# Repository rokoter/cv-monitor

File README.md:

# CV-monitor

Herbruikbaar ESP32-S3-sensorbord voor Home Assistant (ESPHome). Twee algemene temperatuurpoorten (TEMP 1/2,
DS18B20); eerste toepassing: aanvoer- en retourtemperatuur van de CV-installatie. Voeding via USB-C met een 18650 als
UPS-backup. Uitbreidbaar via Qwiic (I²C), een uitbreidingsheader en aansluitingen voor OLED en e-ink.

Leertraject: Koen stuurt en controleert, Claude voert uit.

## Status
| Stap | Status |
|------|--------|
| 1. Schema (KiCad) | rev 0.8 akkoord – nieuw: Resol VBus-ingang (opto-geïsoleerd) en 2 relaiskanalen, Finder 34.51 op het bord en/of extern (`docs/schema_blok10_11_vbus_relais.png`) |
| 2. PCB-layout | rev 0.3 (100 × 100 mm, VBus + relais): plaatsing in review – `docs/pcb_plaatsing_rev0.3.png`, `docs/pcb_preview_*_rev0.3.png`, 3D: `docs/pcb_3d_*_rev0.3.png`; routing volgt na akkoord. rev 0.2 (gerouteerd, DRC 0/0) is niet besteld en vervalt |
| 3. JLCPCB productie (Gerber, BOM, CPL) | rev 0.2 klaar voor offerte: Economic PCBA, ESP + through-hole zelf – `hardware/cv_monitor/production/README.md`, kosten: `docs/KOSTEN.md` |
| 4. Firmware (ESPHome) | – |
| 5. Behuizing (FreeCAD) | – |

## Mappen
| Map | Inhoud |
|-----|--------|
| `hardware/cv_monitor/` | KiCad-project (open `cv_monitor.kicad_pro`); details in de README daar |
| `generator/` | Scripts die schema en bibliotheek opbouwen en controleren (`design.py` = het ontwerp in tekst) |
| `docs/` | Schema-PDF en uitleg (draw.io) |
| `firmware/` | ESPHome-configuratie (volgt) |
| `enclosure/` | FreeCAD-behuizing (volgt) |

## PCB opnieuw genereren: plaatsing + routing
```bash
P=hardware/cv_monitor/cv_monitor
kicad-cli sch export netlist -o /tmp/cv_monitor.net $P.kicad_sch
/usr/bin/python3 generator/make_pcb.py /tmp/cv_monitor.net $P.kicad_pcb      # plaatsing + silkscreen
/usr/bin/python3 generator/route.py prep $P.kicad_pcb $P.dsn                 # vlakken, keepouts, fanout, DSN
xvfb-run -a java -jar freerouting.jar -de $P.dsn -dr generator/freerouting.rules -do $P.ses -mp 80 -mt 1
/usr/bin/python3 generator/route.py import $P.kicad_pcb $P.ses               # sporen + GND-vulling
/usr/bin/python3 generator/drc.py $P.kicad_pcb                               # moet 0 / 0 geven
/usr/bin/python3 generator/route_report.py $P.kicad_pcb                      # lengtes, breedtes, controles
```
- Plaatsing: `generator/placement.py`; ontwerpregels en netklassen: `generator/rules.py`.
- Lagen: F.Cu signaal + GND-vulling | In1 GND-vlak | In2 3V3-vlak | B.Cu signaal + GND-vulling.
- Netklassen: standaard 0,2 mm (0,15 mm vrij), 5V/VSYS/accu 0,8 mm, USB-ingang 0,5 mm, B− 0,4 mm,
  GND/3V3 0,4 mm, USB D+/D− als differentieel paar 0,25/0,15 mm (~90 Ω, schatting); via's 0,6/0,3 mm
  (vermogen 0,8/0,4 mm).
- USB: vast voorgerouteerd (`fanout.usb_preroute`): USB-C → ESD-chip U1 (180° gedraaid, zodat D−/D+
  zonder kruising doorlopen) → paar over de onderkant → ESP-pin 13/14; ~79 mm, lengteverschil < 0,5 mm.
- `route.py prep` geeft elke SMD-pad op GND/3V3 een eigen via naar het vlak (`generator/fanout.py`),
  legt de dubbele USB-C-datapinnen vast en houdt de antennezone (alle lagen) en de bovenlaag onder
  de ESP-module vrij van sporen. Freerouting (v1.9.0, open source) routeert de rest.
- Koperlagen als plaatje: `generator/render_layers.sh $P.kicad_pcb docs rev0.3`.

3D: alle footprints staan in de projectbibliotheek `cv_monitor.pretty` en de 3D-modellen (STEP) in
`hardware/cv_monitor/3dmodels` (zie de README daar). In KiCad: **Beeld → 3D-viewer** (Alt+3).
Bord met onderdelen (rev 0.3): 100 × 100 × 35,8 mm (19,1 mm onder het bord door accuhouder + cel, 15,1 mm
erboven door de relais). Snelle preview zonder KiCad: `kicad-cli pcb export step` en `generator/render_3d.py` →
`docs/pcb_3d_boven_rev0.3.png` en `docs/pcb_3d_onder_rev0.3.png`.

Plaatsingsafspraken (worden door `drc.py` mee gecontroleerd):
- alle R's, C's, diodes en LED's horizontaal (0° of 180°), kleine onderdelen in nette rijen/kolommen;
- alle silkscreentekst horizontaal, leesbaar vanuit één kant (boven: van voren, onder: met het bord omgedraaid);
- referentie bij voorkeur recht boven/onder/links/rechts van het eigen onderdeel, binnen de bordrand;
- pinnamen van headers en klemmen op de bovenkant (waar je aansluit), één naam per regel links van de pin;
- polariteit (+) bij de accu en bij de accu-omgekeerd-LED, op boven- en onderkant;
- achterkant: blokschema van de werking (`generator/back_diagram.py`), titel bovenaan tussen de montagegaten;
- geen THT-pin door een onderdeel aan de andere kant (accuhouder);
- 230 V (relaiscontacten NO/COM/NC + klemmen J12/J13): gestippeld kader op boven- en onderkant met
  '230V~ 5A', en al het koper van andere netten (alle lagen, ook gaten) minstens 8 mm van het 230 V-koper
  (`pcb_checks.mains_clearance`; krapste plek nu 8,3 mm: spoelpad K1.A2 ↔ NO-pad K2).

## Productiebestanden (JLCPCB)
```bash
P=hardware/cv_monitor/cv_monitor
/usr/bin/python3 generator/sync_attrs.py $P.kicad_pcb            # LCSC/DNP uit design.py, routing blijft
/usr/bin/python3 generator/make_production.py $P.kicad_pcb rev0.2  # Gerber-zip, BOM, CPL
```
Uitvoer en bestelchecklist: `hardware/cv_monitor/production/`. JLCPCB-draaiingscorrecties staan in
`make_production.py` (`ROT_FIX`); gepolariseerde onderdelen altijd in de JLCPCB-preview controleren.

## Opnieuw bouwen en controleren
```bash
./generator/build.sh
```
Genereert het schema uit `generator/design.py`, laat KiCad de netlist exporteren en vergelijkt die
pin voor pin met de bedoeling (kortsluitingen, losse pinnen, voeding). Daarnaast: ERC in KiCad zelf.

## KiCad-versie
De bestanden worden gemaakt met **KiCad 7.0** (het formaat dat de generator schrijft). Openen, bekijken
en ERC draaien kan prima in KiCad 8, 9 of 10. **Sla ze in een nieuwere versie niet op over de repo-bestanden**:
KiCad zet ze dan om naar het nieuwe formaat, dat KiCad 7 niet meer kan lezen. Wil je iets aanpassen,
geef het door (of sla op als kopie); de wijziging komt dan via `design.py` in het ontwerp.

## Werkwijze
- Elke ontwerpwijziging is een eigen commit; goedgekeurde stappen krijgen een tag (bijv. `schema-v1.0`).
- Wijzig het schema bij voorkeur via `design.py` + `build.sh`, zodat de controle blijft kloppen.
  Handmatige aanpassingen in KiCad kunnen ook, maar worden bij een volgende generatie overschreven.

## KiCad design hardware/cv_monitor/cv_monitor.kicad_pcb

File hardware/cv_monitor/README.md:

# CV temperatuurmonitor – stap 1: schema (rev 0.8)

Herbruikbaar ESP32-S3-sensorbord: meet 2 temperaturen met DS18B20's (bijv. CV-aanvoer en -retour),
heeft een 18650 als UPS-backup, laadt/werkt via USB-C en heeft aansluitingen voor Qwiic-modules,
een OLED (I²C) en een e-ink-display (SPI). Sinds rev 0.8 ook een Resol VBus-ingang (zonne-/boilerregelaar)
en 2 relaisuitgangen (relais op het bord en/of extern).

## Openen
Pak de map uit en open `cv_monitor.kicad_pro` in KiCad (7, 8 of 9). De projectbibliotheken
(`cv_monitor.kicad_sym`, `cv_monitor.pretty`) worden via `sym-lib-table`/`fp-lib-table` automatisch geladen.
Gemaakt in KiCad 7-formaat; KiCad 8/9 vraagt bij opslaan om te converteren – dat is prima.

## Blokken
| # | Blok | Kern |
|---|------|------|
| 1 | USB-C | 1,1 A PTC-zekering, 5,1k CC-weerstanden, USBLC6 ESD op D+/D- (native USB) |
| 2 | Lader | TP4056, 600 mA (R3 = 2k), rode/groene LED, optionele NTC op J9 (JP1 doorsnijden) |
| 3 | Power-path | SS34 + AO3401A: USB voedt systeem, accu neemt naadloos over; AP2112K-3.3 LDO |
| 4 | Accu | 18650 + ompoolbeveiliging (Q3) + fout-LED D5 + DW01A + AO8810 (8205A-type dubbele MOSFET; onder-/overspanning, overstroom) |
| 5 | ESP32-S3-WROOM-1-N8 | 8 MB flash, alle GPIO's op het symbool |
| 6 | Metingen | VBAT, USB aanwezig, 2 sensorpoorten (4,7k pull-up, 100R serie) |
| 7 | Bediening | RESET, BOOT, STATUS-knop, status-LED, uitbreidingsheader J4 (DNP) |
| 8 | Qwiic | 2× JST-SH, I²C met 4,7k pull-ups |
| 9 | Displays | J8 e-ink (SPI, Waveshare-volgorde), J7 OLED (I²C) – beide DNP |
| 10 | Resol VBus | J10, opto-coupler U6 (LTV-817S): alleen lezen, Resol-massa gescheiden van GND, RX = GPIO38 |
| 11 | Relais | 2× AO3400A (GPIO35/36) + vrijloop + status-LED; per kanaal Finder 34.51 (5 V) op het bord (J12/J13, 230 V~ max 5 A) en/of extern relais op J11 (V+/REL1/REL2/GND) |
| – | Testpunten | TP1–TP5: VBUS, VSYS, BAT+, 3V3, GND (alleen koperpads) |

## GPIO-overzicht (ESP32-S3)
| GPIO | Functie | GPIO | Functie |
|------|---------|------|---------|
| 0 | BOOT-knop | 13 | e-ink DC |
| 1 | VBAT meting (ADC1) | 14 | e-ink RST |
| 2 | USB aanwezig (ADC1) | 15 | STATUS-knop |
| 3 | vrij (strapping) | 16 | status-LED |
| 35/36 | relais 1/2 | 38 | Resol VBus RX |
| 4 | TEMP 1 (1-Wire) | 17/18 | uitbreiding J4 |
| 5 | TEMP 2 (1-Wire) | 19/20 | USB D-/D+ |
| 6/7 | uitbreiding J4 (ADC1) | 21 | e-ink BUSY |
| 8 | I²C SDA (Qwiic + OLED) | 43/44 | UART TX/RX (J4) |
| 9 | I²C SCL (Qwiic + OLED) | 45/46 | vrij (strapping) |
| 10 | e-ink CS | overige | vrij (X op schema) |
| 11 | e-ink DIN (MOSI) | | |
| 12 | e-ink CLK | | |

## Controle door jou
1. Open het schema en draai **Inspect → Electrical Rules Checker**. Verwacht: 0 fouten.
2. Loop elk blok na met de notities op het blad.
3. LCSC-nummers staan als veld `LCSC` per onderdeel; die worden in de BOM-stap opnieuw gecontroleerd.

## Gebruik / aandachtspunten
- Voeding via een USB-lader van minimaal 1 A (laden 0,6 A + systeem); een pc-poort levert te weinig.
- Na het plaatsen van de accu één keer USB aansluiten: dan activeert de DW01A de accu-uitgang.
- Accuhouder: MPD BK-18650-PC2 (de footprint past alleen op deze houder).
- Accu-NTC (optioneel): stekker in J9 aan de bovenkant, de draad door de sleuf (4 × 7 mm) eronder naar
  de onderkant en de NTC met kaptontape midden op de cel. Bij gebruik van een NTC: JP1 doorsnijden.
  De sleuf is groot genoeg om ook een JST-PH-stekkertje in de lengte door te steken.

## Productie
Gerber, BOM, CPL en de bestelchecklist voor JLCPCB: `production/README.md`.
Gekozen: accuhouder MPD BK-18650-PC2, schroefklemmen 3,5 mm; J7/J8 volgen de pinvolgorde van een
0,96" SSD1306-OLED (GND-VCC-SCL-SDA) en een Waveshare 2,9" e-Paper V2 (8-pins).

## Documentatie
- `../../docs/accubeveiliging_DW01A_FS8205A.drawio`: uitleg hoe de accubeveiliging werkt (openen op app.diagrams.net).

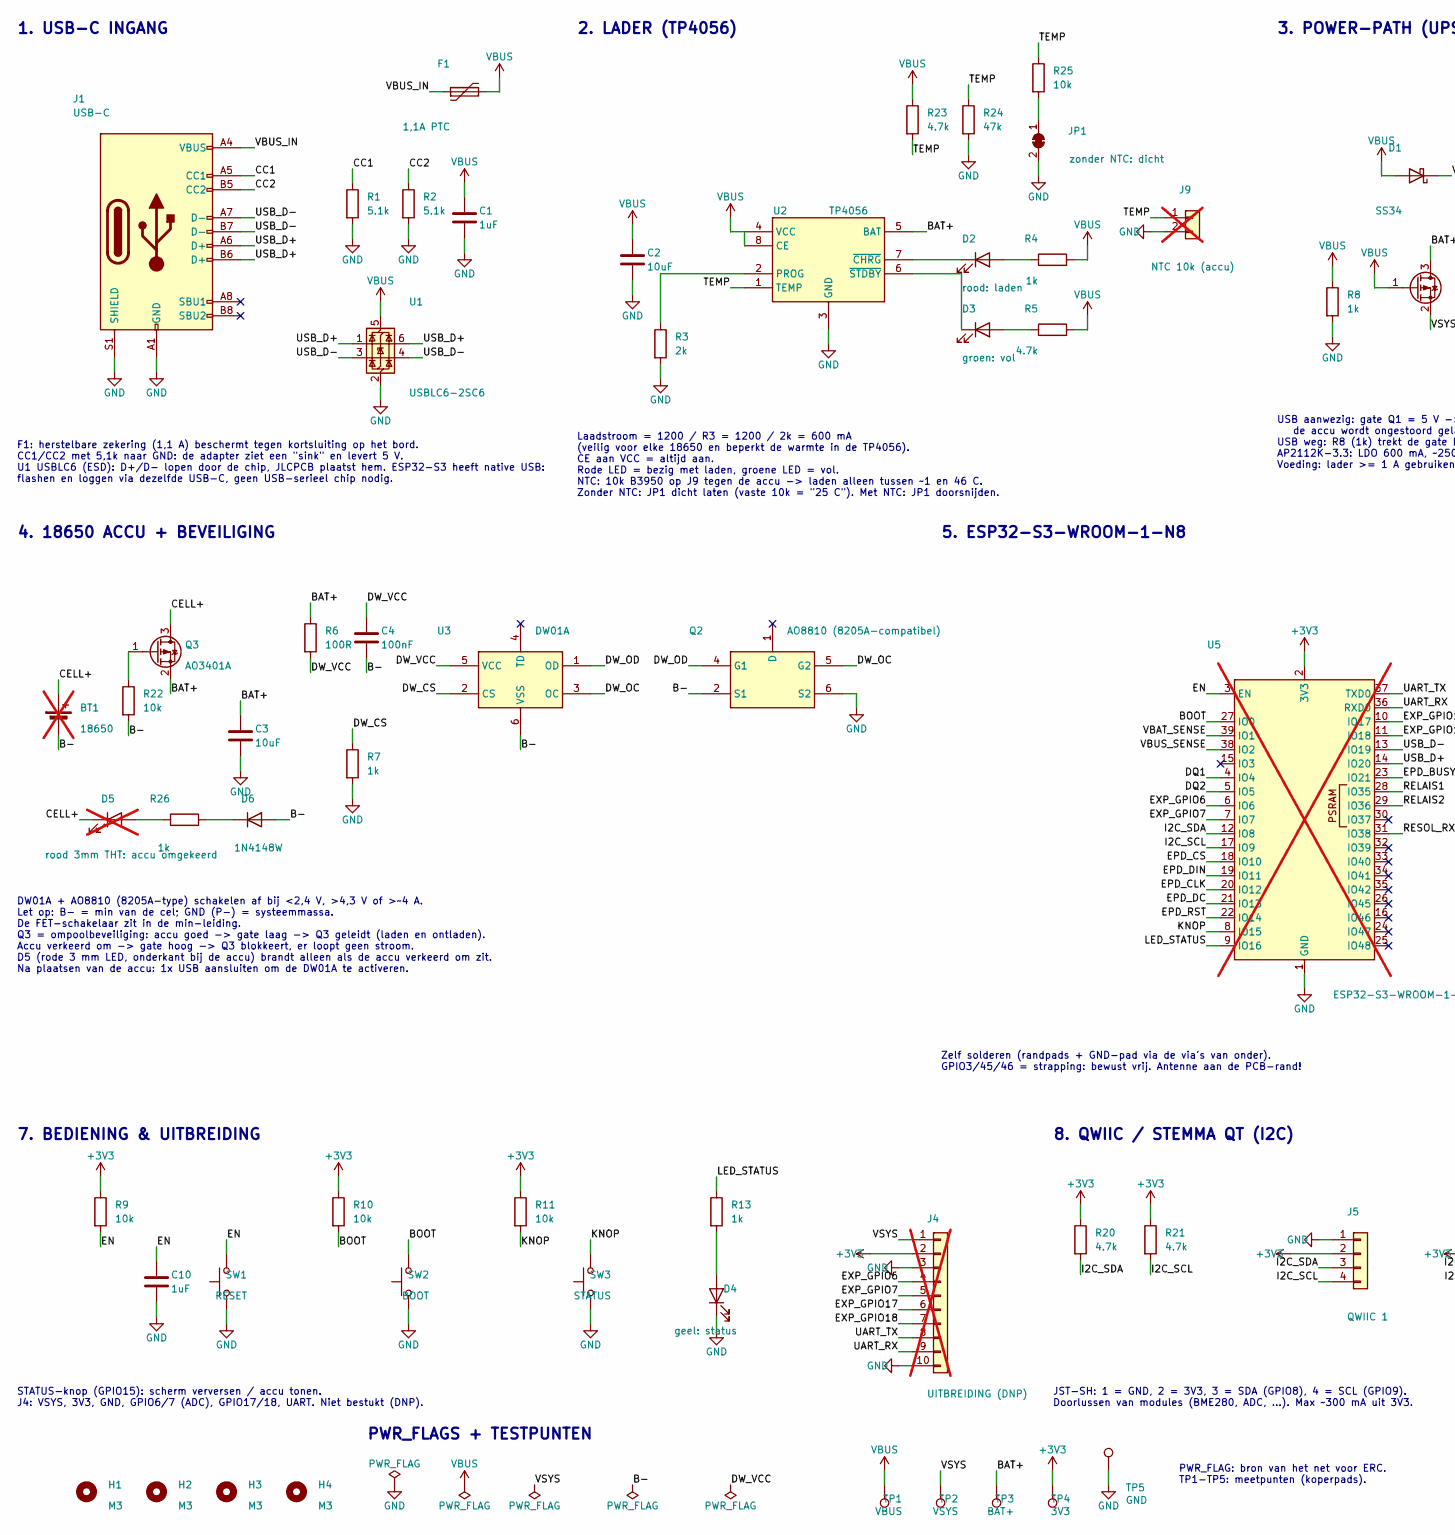
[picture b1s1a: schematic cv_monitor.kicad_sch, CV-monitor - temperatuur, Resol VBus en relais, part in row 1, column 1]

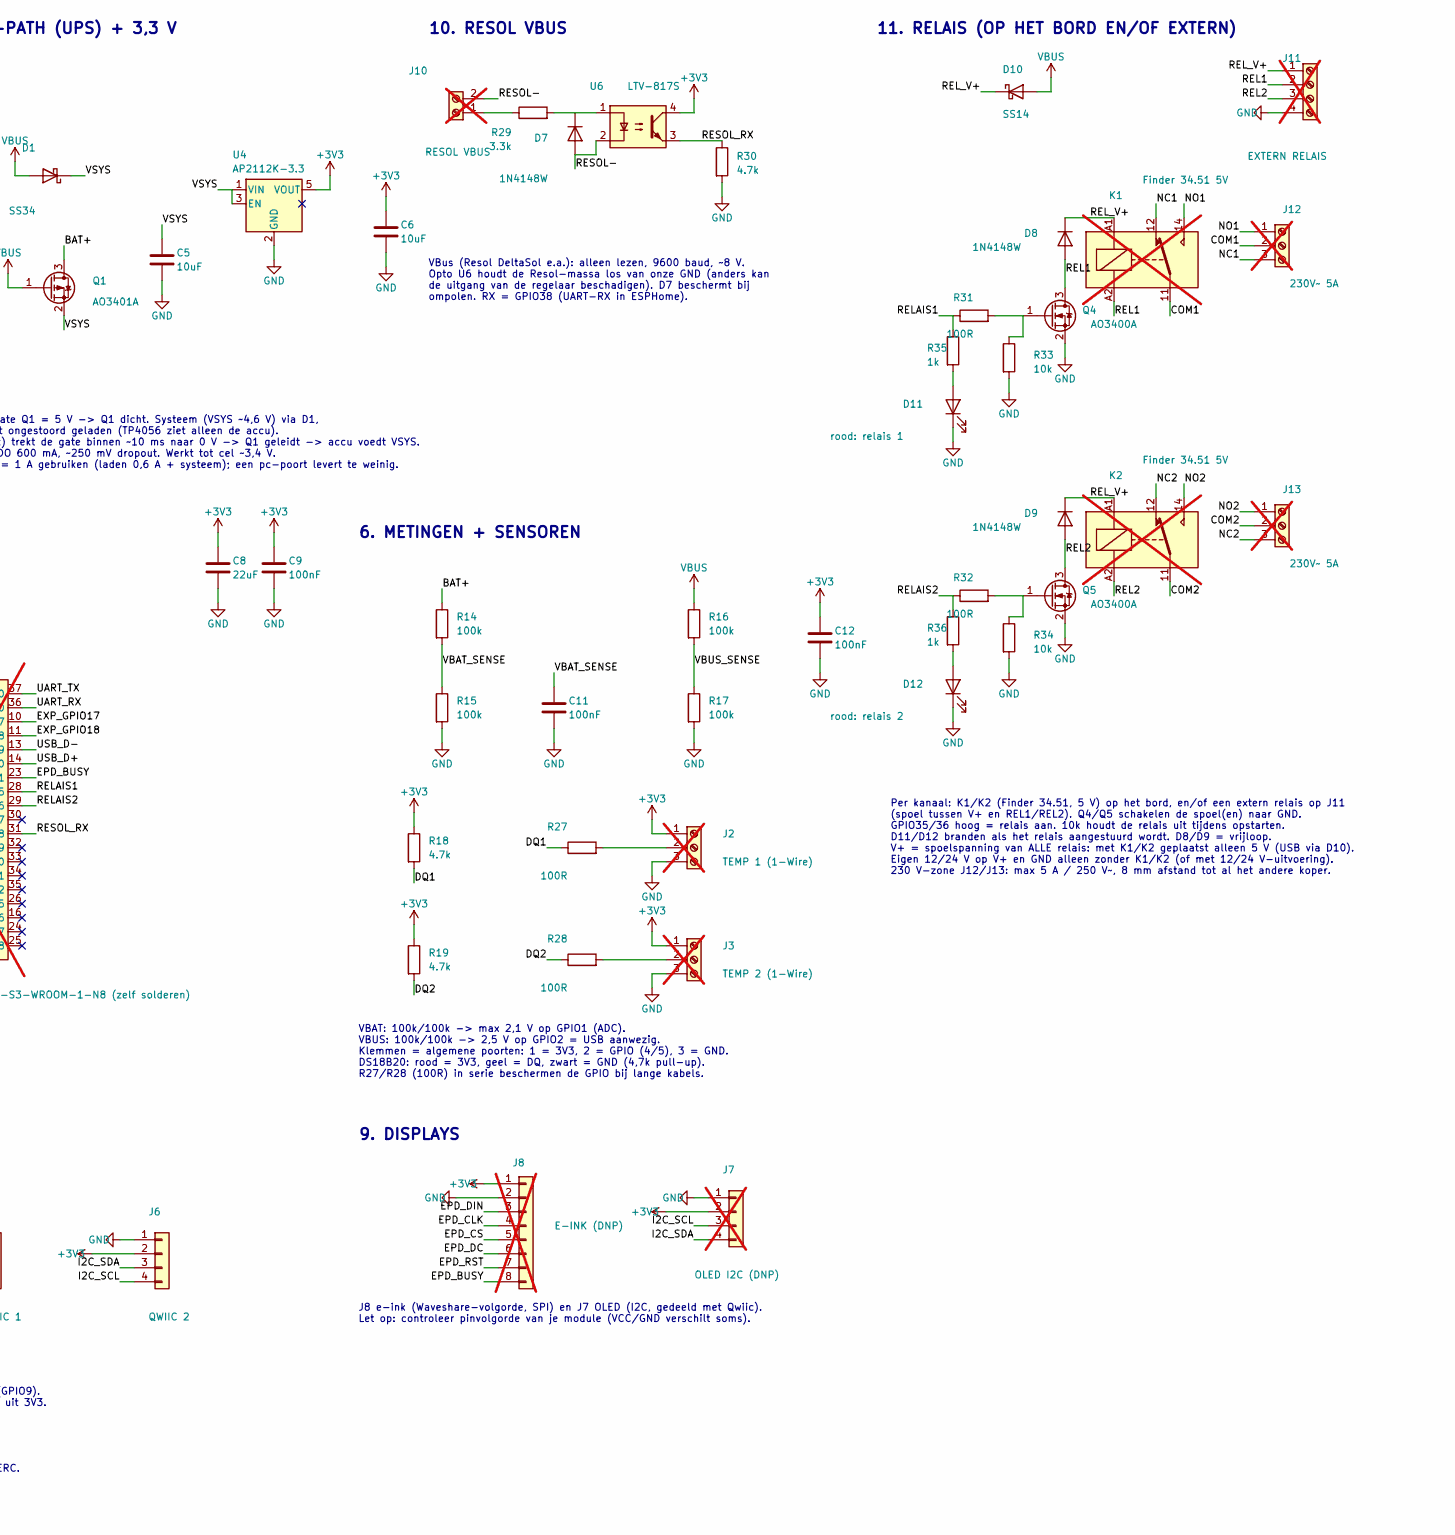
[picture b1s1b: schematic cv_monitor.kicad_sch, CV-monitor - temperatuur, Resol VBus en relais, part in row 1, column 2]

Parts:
BT1: 18650; BatteryHolder_MPD_BH-18650-PC2; MPN houder MPD BK-18650-PC2; not fitted
C1, C10: 1uF; C_0603_1608Metric; LCSC C15849
C2, C3, C5, C6: 10uF; C_0805_2012Metric; LCSC C15850
C4, C9, C11, C12: 100nF; C_0603_1608Metric; LCSC C14663
C8: 22uF; C_0805_2012Metric; LCSC C45783
D1: SS34; D_SMA; LCSC C8678
D2: rood: laden; LED_0603_1608Metric; LCSC C2286
D3: groen: vol; LED_0603_1608Metric; LCSC C12624
D4: geel: status; LED_0603_1608Metric; LCSC C89811
D5: rood 3mm THT: accu omgekeerd; LED_D3.0mm; not fitted
D6, D7, D8, D9: 1N4148W; D_SOD-123; LCSC C81598
D10: SS14; D_SMA; LCSC C2480
D11: rood: relais 1; LED_0603_1608Metric; LCSC C2286
D12: rood: relais 2; LED_0603_1608Metric; LCSC C2286
F1: 1,1A PTC; Fuse_1206_3216Metric; LCSC C269119
H1, H2, H3, H4: M3; MountingHole_3.2mm_M3
J1: USB-C; USB_C_Receptacle_HRO_TYPE-C-31-M-12; LCSC C165948
J2: TEMP 1 (1-Wire); TerminalBlock_Phoenix_PT-1,5-3-3.5-H_1x03_P3.50mm_Horizontal; not fitted
J3: TEMP 2 (1-Wire); TerminalBlock_Phoenix_PT-1,5-3-3.5-H_1x03_P3.50mm_Horizontal; not fitted
J4: UITBREIDING (DNP); PinHeader_1x10_P2.54mm_Vertical; not fitted
J5: QWIIC 1; JST_SH_SM04B-SRSS-TB_1x04-1MP_P1.00mm_Horizontal; LCSC C160404
J6: QWIIC 2; JST_SH_SM04B-SRSS-TB_1x04-1MP_P1.00mm_Horizontal; LCSC C160404
J7: OLED I2C (DNP); PinHeader_1x04_P2.54mm_Vertical; not fitted
J8: E-INK (DNP); PinHeader_1x08_P2.54mm_Vertical; not fitted
J9: NTC 10k (accu); JST_PH_B2B-PH-K_1x02_P2.00mm_Vertical; not fitted
J10: RESOL VBUS; TerminalBlock_Phoenix_PT-1,5-2-3.5-H_1x02_P3.50mm_Horizontal; not fitted
J11: EXTERN RELAIS; TerminalBlock_Phoenix_PT-1,5-4-3.5-H_1x04_P3.50mm_Horizontal; not fitted
J12, J13: 230V~ 5A; TerminalBlock_Phoenix_MKDS-1,5-3-5.08_1x03_P5.08mm_Horizont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; MPN Phoenix MKDS 1,5/3-5,08; not fitted
JP1: zonder NTC: dicht; SolderJumper-2_P1.3mm_Bridged_RoundedPad1.0x1.5mm
K1, K2: Finder 34.51 5V; Relay_SPDT_Finder_34.51_Vertical; MPN Finder 34.51.7.005.0010; not fitted
Q1, Q3: AO3401A; SOT-23; LCSC C15127
Q2: AO8810 (8205A-compatibel); TSSOP-8_4.4x3mm_P0.65mm; LCSC C21426
Q4, Q5: AO3400A; SOT-23; LCSC C20917
R1, R2: 5.1k; R_0603_1608Metric; LCSC C23186
R3: 2k; R_0603_1608Metric; LCSC C22975
R4, R7, R8, R13, R26, R35, R36: 1k; R_0603_1608Metric; LCSC C21190
R5, R18, R19, R20, R21, R23, R30: 4.7k; R_0603_1608Metric; LCSC C23162
R6, R27, R28, R31, R32: 100R; R_0603_1608Metric; LCSC C22775
R9, R10, R11, R22, R25, R33, R34: 10k; R_0603_1608Metric; LCSC C25804
R14, R15, R16, R17: 100k; R_0603_1608Metric; LCSC C25803
R24: 47k; R_0603_1608Metric; LCSC C25819
R29: 3.3k; R_0603_1608Metric; LCSC C22978
SW1: RESET; SW_Push_1P1T_XKB_TS-1187A; LCSC C318884
SW2: BOOT; SW_Push_1P1T_XKB_TS-1187A; LCSC C318884
SW3: STATUS; SW_Push_1P1T_XKB_TS-1187A; LCSC C318884
TP1: VBUS; TestPoint_Pad_D1.5mm
TP2: VSYS; TestPoint_Pad_D1.5mm
TP3: BAT+; TestPoint_Pad_D1.5mm
TP4: 3V3; TestPoint_Pad_D1.5mm
TP5: GND; TestPoint_Pad_D1.5mm
U1: USBLC6-2SC6; SOT-23-6; LCSC C7519
U2: TP4056; SOIC-8-1EP_3.9x4.9mm_P1.27mm_EP2.41x3.3mm_ThermalVias_0.3mm; LCSC C16581
U3: DW01A; SOT-23-6; LCSC C351410
U4: AP2112K-3.3; SOT-23-5; LCSC C51118
U5: ESP32-S3-WROOM-1-N8 (zelf solderen); ESP32-S3-WROOM-1_HandSolder; LCSC C2913198; not fitted
U6: LTV-817S; SMDIP-4_W9.53mm; LCSC C109227

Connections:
+3V3: C6.1, C8.1, C9.1, C12.1, J2.1, J3.1, J4.2, J5.2, J6.2, J7.2, J8.1, R9.1, R10.1, R11.1, R18.1, R19.1, R20.1, R21.1, TP4.1, U4.5 (VOUT), U5.2 (3V3), U6.4
B-: BT1.2 (-), C4.2, D6.2 (A), Q2.2 (S1), Q2.3 (S1), R22.2, U3.6 (VSS)
BAT+: C3.1, Q1.3 (D), Q3.2 (S), R6.1, R14.1, TP3.1, U2.5 (BAT)
BOOT: R10.2, SW2.2, U5.27 (IO0)
CC1: J1.A5 (CC1), R1.1
CC2: J1.B5 (CC2), R2.1
CELL+: BT1.1 (+), D5.1 (K), Q3.3 (D)
COM1: J12.2, K1.11
COM2: J13.2, K2.11
DQ1: R18.2, R27.1, U5.4 (IO4)
DQ2: R19.2, R28.1, U5.5 (IO5)
DW_CS: R7.1, U3.2 (CS)
DW_OC: Q2.5 (G2), U3.3 (OC)
DW_OD: Q2.4 (G1), U3.1 (OD)
DW_VCC: C4.1, R6.2, U3.5 (VCC)
EN: C10.1, R9.2, SW1.2, U5.3 (EN)
EPD_BUSY: J8.8, U5.23 (IO21)
EPD_CLK: J8.4, U5.20 (IO12)
EPD_CS: J8.5, U5.18 (IO10)
EPD_DC: J8.6, U5.21 (IO13)
EPD_DIN: J8.3, U5.19 (IO11)
EPD_RST: J8.7, U5.22 (IO14)
EXP_GPIO6: J4.4, U5.6 (IO6)
EXP_GPIO7: J4.5, U5.7 (IO7)
EXP_GPIO17: J4.6, U5.10 (IO17)
EXP_GPIO18: J4.7, U5.11 (IO18)
GND: C1.2, C2.2, C3.2, C5.2, C6.2, C8.2, C9.2, C10.2, C11.2, C12.2, D4.1 (K), D11.1 (K), D12.1 (K), J1.A1 (GND), J1.A12 (GND), J1.B1 (GND), J1.B12 (GND), J1.S1 (SHIELD), J2.3, J3.3, J4.3, J4.10, J5.1, J6.1, J7.1, J8.2, J9.2, J11.4, JP1.2 (B), Q2.6 (S2), Q2.7 (S2), Q4.2 (S), Q5.2 (S), R1.2, R2.2, R3.2, R7.2, R8.2, R15.2, R17.2, R24.2, R30.2, R33.2, R34.2, SW1.1, SW2.1, SW3.1, TP5.1, U1.2 (GND), U2.3 (GND), U2.9 (EP), U4.2 (GND), U5.1 (GND), U5.40 (GND), U5.41 (GND)
I2C_SCL: J5.4, J6.4, J7.3, R21.2, U5.17 (IO9)
I2C_SDA: J5.3, J6.3, J7.4, R20.2, U5.12 (IO8)
KNOP: R11.2, SW3.2, U5.8 (IO15)
LED_STATUS: R13.1, U5.9 (IO16)
NC1: J12.3, K1.12
NC2: J13.3, K2.12
NO1: J12.1, K1.14
NO2: J13.1, K2.14
unnamed: D2.2 (A), R4.1
unnamed: D2.1 (K), U2.7 (~CHRG)
unnamed: D3.2 (A), R5.1
unnamed: D3.1 (K), U2.6 (~STDBY)
unnamed: D4.2 (A), R13.2
unnamed: D5.2 (A), R26.1
unnamed: D6.1 (K), R26.2
unnamed: D7.1 (K), R29.2, U6.1
unnamed: D11.2 (A), R35.2
unnamed: D12.2 (A), R36.2
unnamed: J2.2, R27.2
unnamed: J3.2, R28.2
unnamed: J10.1, R29.1
unnamed: JP1.1 (A), R25.2
unnamed: Q3.1 (G), R22.1
unnamed: Q4.1 (G), R31.2, R33.1
unnamed: Q5.1 (G), R32.2, R34.1
unnamed: R3.1, U2.2 (PROG)
REL1: D8.2 (A), J11.2, K1.A2, Q4.3 (D)
REL2: D9.2 (A), J11.3, K2.A2, Q5.3 (D)
RELAIS1: R31.1, R35.1, U5.28 (IO35)
RELAIS2: R32.1, R36.1, U5.29 (IO36)
REL_V+: D8.1 (K), D9.1 (K), D10.1 (K), J11.1, K1.A1, K2.A1
RESOL-: D7.2 (A), J10.2, U6.2
RESOL_RX: R30.1, U5.31 (IO38), U6.3
TEMP: J9.1, R23.2, R24.1, R25.1, U2.1 (TEMP)
UART_RX: J4.9, U5.36 (RXD0)
UART_TX: J4.8, U5.37 (TXD0)
USB_D+: J1.A6 (D+), J1.B6 (D+), U1.1 (I/O1), U1.6 (I/O1), U5.14 (IO20)
USB_D-: J1.A7 (D-), J1.B7 (D-), U1.3 (I/O2), U1.4 (I/O2), U5.13 (IO19)
VBAT_SENSE: C11.1, R14.2, R15.1, U5.39 (IO1)
VBUS: C1.1, C2.1, D1.2 (A), D10.2 (A), F1.2, Q1.1 (G), R4.2, R5.2, R8.1, R16.1, R23.1, TP1.1, U1.5 (VBUS), U2.4 (VCC), U2.8 (CE)
VBUS_IN: F1.1, J1.A4 (VBUS), J1.A9 (VBUS), J1.B4 (VBUS), J1.B9 (VBUS)
VBUS_SENSE: R16.2, R17.1, U5.38 (IO2)
VSYS: C5.1, D1.1 (K), J4.1, Q1.2 (S), TP2.1, U4.1 (VIN), U4.3 (EN)

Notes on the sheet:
1. USB-C INGANG
F1: herstelbare zekering (1,1 A) beschermt tegen kortsluiting op het bord. CC1/CC2 met 5,1k naar GND: de adapter ziet een "sink" en levert 5 V. U1 USBLC6 (ESD): D+/D- lopen door de chip, JLCPCB plaatst hem. ESP32-S3 heeft native USB: flashen en loggen via dezelfde USB-C, geen USB-serieel chip nodig.
2. LADER (TP4056)
Laadstroom = 1200 / R3 = 1200 / 2k = 600 mA (veilig voor elke 18650 en beperkt de warmte in de TP4056). CE aan VCC = altijd aan. Rode LED = bezig met laden, groene LED = vol. NTC: 10k B3950 op J9 tegen de accu -> laden alleen tussen ~1 en 46 C. Zonder NTC: JP1 dicht laten (vaste 10k = "25 C"). Met 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
3. POWER-PATH (UPS) + 3,3 V
USB aanwezig: gate Q1 = 5 V -> Q1 dicht. Systeem (VSYS ~4,6 V) via D1, de accu wordt ongestoord geladen (TP4056 ziet alleen de accu). USB weg: R8 (1k) trekt de gate binnen ~10 ms naar 0 V -> Q1 geleidt -> accu voedt VSYS. AP2112K-3.3: LDO 600 mA, ~250 mV dropout. Werkt tot cel ~3,4 V. Voeding: lade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
PWR_FLAGS + TESTPUNTEN
PWR_FLAG: bron van het net voor ERC. TP1-TP5: meetpunten (koperpads).
10. RESOL VBUS
VBus (Resol DeltaSol e.a.): alleen lezen, 9600 baud, ~8 V. Opto U6 houdt de Resol-massa los van onze GND (anders kan de uitgang van de regelaar beschadigen). D7 beschermt bij ompolen. RX = GPIO38 (UART-RX in ESPHome).
11. RELAIS (OP HET BORD EN/OF EXTERN)
Per kanaal: K1/K2 (Finder 34.51, 5 V) op het bord, en/of een extern relais op J11 (spoel tussen V+ en REL1/REL2). Q4/Q5 schakelen de spoel(en) naar GND. GPIO35/36 hoog = relais aan. 10k houdt de relais uit tijdens opstarten. D11/D12 branden als het relais aangestuurd wordt. D8/D9 = vrijloop. V+ = s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
4. 18650 ACCU + BEVEILIGING
DW01A + AO8810 (8205A-type) schakelen af bij <2,4 V, >4,3 V of >~4 A. Let op: B- = min van de cel; GND (P-) = systeemmassa. De FET-schakelaar zit in de min-leiding. Q3 = ompoolbeveiliging: accu goed -> gate laag -> Q3 geleidt (laden en ontladen). Accu verkeerd om -> gate hoog -> Q3 blokkeert, er lo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
5. ESP32-S3-WROOM-1-N8
Zelf solderen (randpads + GND-pad via de via's van onder). GPIO3/45/46 = strapping: bewust vrij. Antenne aan de PCB-rand!
6. METINGEN + SENSOREN
VBAT: 100k/100k -> max 2,1 V op GPIO1 (ADC). VBUS: 100k/100k -> 2,5 V op GPIO2 = USB aanwezig. Klemmen = algemene poorten: 1 = 3V3, 2 = GPIO (4/5), 3 = GND. DS18B20: rood = 3V3, geel = DQ, zwart = GND (4,7k pull-up). R27/R28 (100R) in serie beschermen de GPIO bij lange kabels.
7. BEDIENING & UITBREIDING
STATUS-knop (GPIO15): scherm verversen / accu tonen. J4: VSYS, 3V3, GND, GPIO6/7 (ADC), GPIO17/18, UART. Niet bestukt (DNP).
8. QWIIC / STEMMA QT (I2C)
JST-SH: 1 = GND, 2 = 3V3, 3 = SDA (GPIO8), 4 = SCL (GPIO9). Doorlussen van modules (BME280, ADC, ...). Max ~300 mA uit 3V3.
9. DISPLAYS
J8 e-ink (Waveshare-volgorde, SPI) en J7 OLED (I2C, gedeeld met Qwiic). Let op: controleer pinvolgorde van je module (VCC/GND verschilt soms).

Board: 4 copper layers, 99 parts (2 on the bottom side), 70 nets, no tracks yet.

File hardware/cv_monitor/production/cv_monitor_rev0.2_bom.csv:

Comment,Designator,Footprint,LCSC Part #
1uF,"C1,C10",C_0603_1608Metric,C15849
10uF,"C2,C3,C5,C6",C_0805_2012Metric,C15850
100nF,"C4,C9,C11,C12",C_0603_1608Metric,C14663
22uF,C8,C_0805_2012Metric,C45783
SS34,D1,D_SMA,C8678
rood: laden,D2,LED_0603_1608Metric,C2286
groen: vol,D3,LED_0603_1608Metric,C12624
geel: status,D4,LED_0603_1608Metric,C89811
1N4148W,D6,D_SOD-123,C81598
"1,1A PTC",F1,Fuse_1206_3216Metric,C269119
USB-C,J1,USB_C_Receptacle_HRO_TYPE-C-31-M-12,C165948
QWIIC 1 / QWIIC 2,"J5,J6",JST_SH_SM04B-SRSS-TB_1x04-1MP_P1.00mm_Horizontal,C160404
AO3401A,"Q1,Q3",SOT-23,C15127
AO8810 (8205A-compatibel),Q2,TSSOP-8_4.4x3mm_P0.65mm,C21426
5.1k,"R1,R2",R_0603_1608Metric,C23186
2k,R3,R_0603_1608Metric,C22975
1k,"R4,R7,R8,R13,R26",R_0603_1608Metric,C21190
4.7k,"R5,R18,R19,R20,R21,R23",R_0603_1608Metric,C23162
100R,"R6,R27,R28",R_0603_1608Metric,C22775
10k,"R9,R10,R11,R22,R25",R_0603_1608Metric,C25804
100k,"R14,R15,R16,R17",R_0603_1608Metric,C25803
47k,R24,R_0603_1608Metric,C25819
RESET / BOOT / STATUS,"SW1,SW2,SW3",SW_Push_1P1T_XKB_TS-1187A,C318884
USBLC6-2SC6,U1,SOT-23-6,C7519
TP4056,U2,SOIC-8-1EP_3.9x4.9mm_P1.27mm_EP2.41x3.3mm_ThermalVias_0.3mm,C16581
DW01A,U3,SOT-23-6,C351410
AP2112K-3.3,U4,SOT-23-5,C51118

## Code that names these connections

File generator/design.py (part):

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         fp='cv_monitor:ESP32-S3-WROOM-1_HandSolder', lcsc='C2913198', dnp=True, ref_at=(89, 49.5), val_at=(98, 74.5),
         nets={'2': '+3V3', '1': 'GND', '40': 'GND', '41': 'GND', '3': 'EN', '27': 'BOOT',
               '39': 'VBAT_SENSE', '38': 'VBUS_SENSE', '15': 'NC', '4': 'DQ1', '5': 'DQ2',
               '6': 'EXP_GPIO6', '7': 'EXP_GPIO7', '12': 'I2C_SDA', '17': 'I2C_SCL',
               '18': 'EPD_CS', '19': 'EPD_DIN', '20': 'EPD_CLK', '21': 'EPD_DC', '22': 'EPD_RST',
               '8': 'KNOP', '9': 'LED_STATUS', '10': 'EXP_GPIO17', '11': 'EXP_GPIO18',
               '13': 'USB_D-', '14': 'USB_D+', '23': 'EPD_BUSY', '37': 'UART_TX', '36': 'UART_RX',
               '28': 'RELAIS1', '29': 'RELAIS2', '31': 'RESOL_RX',
               **{n: 'NC' for n in ['16', '24', '25', '26', '30', '32', '33', '34', '35']}}),
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    dict(ref='J4', lib='Connector_Generic:Conn_01x10', value='UITBREIDING (DNP)', gx=70, gy=96, dnp=True,
         pwr_rotate=True, stub={'2': 7.62}, fp='Connector_PinHeader_2.54mm:PinHeader_1x10_P2.54mm_Vertical',
         ref_at=(69, 90.5), val_at=(69, 103),
         nets={'1': 'VSYS', '2': '+3V3', '3': 'GND', '4': 'EXP_GPIO6', '5': 'EXP_GPIO7', '6': 'EXP_GPIO17',
               '7': 'EXP_GPIO18', '8': 'UART_TX', '9': 'UART_RX', '10': 'GND'}),

    # ------------------------------------------------------------ 8. Qwiic / STEMMA QT (I2C)
    R('R20', '4.7k', 80, 92, '+3V3', 'I2C_SDA'),
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    dict(ref='D10', lib='Diode:SS14', value='SS14', gx=173, gy=10, fp='Diode_SMD:D_SMA', lcsc='C2480',
         ref_at=(172, 8.4), val_at=(172, 11.6), nets={'1': 'REL_V+', '2': 'VBUS'}),
    # kanaal 1: GPIO -> R31 -> Q4; K1 op het bord en/of extern relais op J11
    R('R31', '100', 170, 26, 'RELAIS1', 'REL1_G', rot=90, label_wired={'1': True},
      ref_at=(170, 24.7), val_at=(170, 27.3)),
    dict(ref='Q4', lib='Transistor_FET:AO3400A', value='AO3400A', gx=175.5, gy=26, fp='Package_TO_SOT_SMD:SOT-23',
         lcsc='C20917', ref_at=(177.7, 25.6), val_at=(178.3, 26.6),
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         extra={'MPN': 'Phoenix MKDS 1,5/3-5,08'}, ref_at=(192, 18.4), val_at=(192.5, 23.7),
         nets={'1': 'NO1', '2': 'COM1', '3': 'NC1'}),
    # kanaal 2: GPIO -> R32 -> Q5; K2 op het bord en/of extern relais op J11
    R('R32', '100', 170, 46, 'RELAIS2', 'REL2_G', rot=90, label_wired={'1': True},
      ref_at=(170, 44.7), val_at=(170, 47.3)),
    dict(ref='Q5', lib='Transistor_FET:AO3400A', value='AO3400A', gx=175.5, gy=46, fp='Package_TO_SOT_SMD:SOT-23',
         lcsc='C20917', ref_at=(177.7, 45.6), val_at=(178.3, 46.6),
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FLAGS = [
    ('power', 'GND', 31, 109.5),
    ('power', 'VBUS', 36, 109.5),
    ('label', 'VSYS', 41, 109.5),
    ('label', 'B-', 48, 109.5),
    ('label', 'DW_VCC', 55, 109.5),
]

TEXTS = [
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           'R27/R28 (100R) in serie beschermen de GPIO bij lange kabels.', gx=126, gy=80.5),

    dict(t='7. BEDIENING & UITBREIDING', gx=4, gy=85, size=2.0, bold=True),
    dict(t='STATUS-knop (GPIO15): scherm verversen / accu tonen.\n'
           'J4: VSYS, 3V3, GND, GPIO6/7 (ADC), GPIO17/18, UART. Niet bestukt (DNP).', gx=4, gy=104),

    dict(t='8. QWIIC / STEMMA QT (I2C)', gx=78, gy=85, size=2.0, bold=True),
    dict(t='JST-SH: 1 = GND, 2 = 3V3, 3 = SDA (GPIO8), 4 = SCL (GPIO9).\n'
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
